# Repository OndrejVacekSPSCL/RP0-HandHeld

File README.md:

# RP0-HandHeld
>*This project was made for HackClub Highway*

Raspberry Pi Zero 2 gaming handheld, that runs Retro Pie...

I always wanted gaming console that has retro games in it so I made this!

## Repository Layout

The repo is structured as follows:
- PCB-related KiCad files in the `PCB/`
- KiCAD case design in `CAD/`
- Software related stuff is located in `Software/`
- For a rough BOM, see `BOM.csv`
- For my development log, see `JOURNAL.md`
- HackClub Readme is located in `README-original.md`
  
> [!CAUTION]
> The physical version of the console is not finished yet! The tutorial will be made after the completation.

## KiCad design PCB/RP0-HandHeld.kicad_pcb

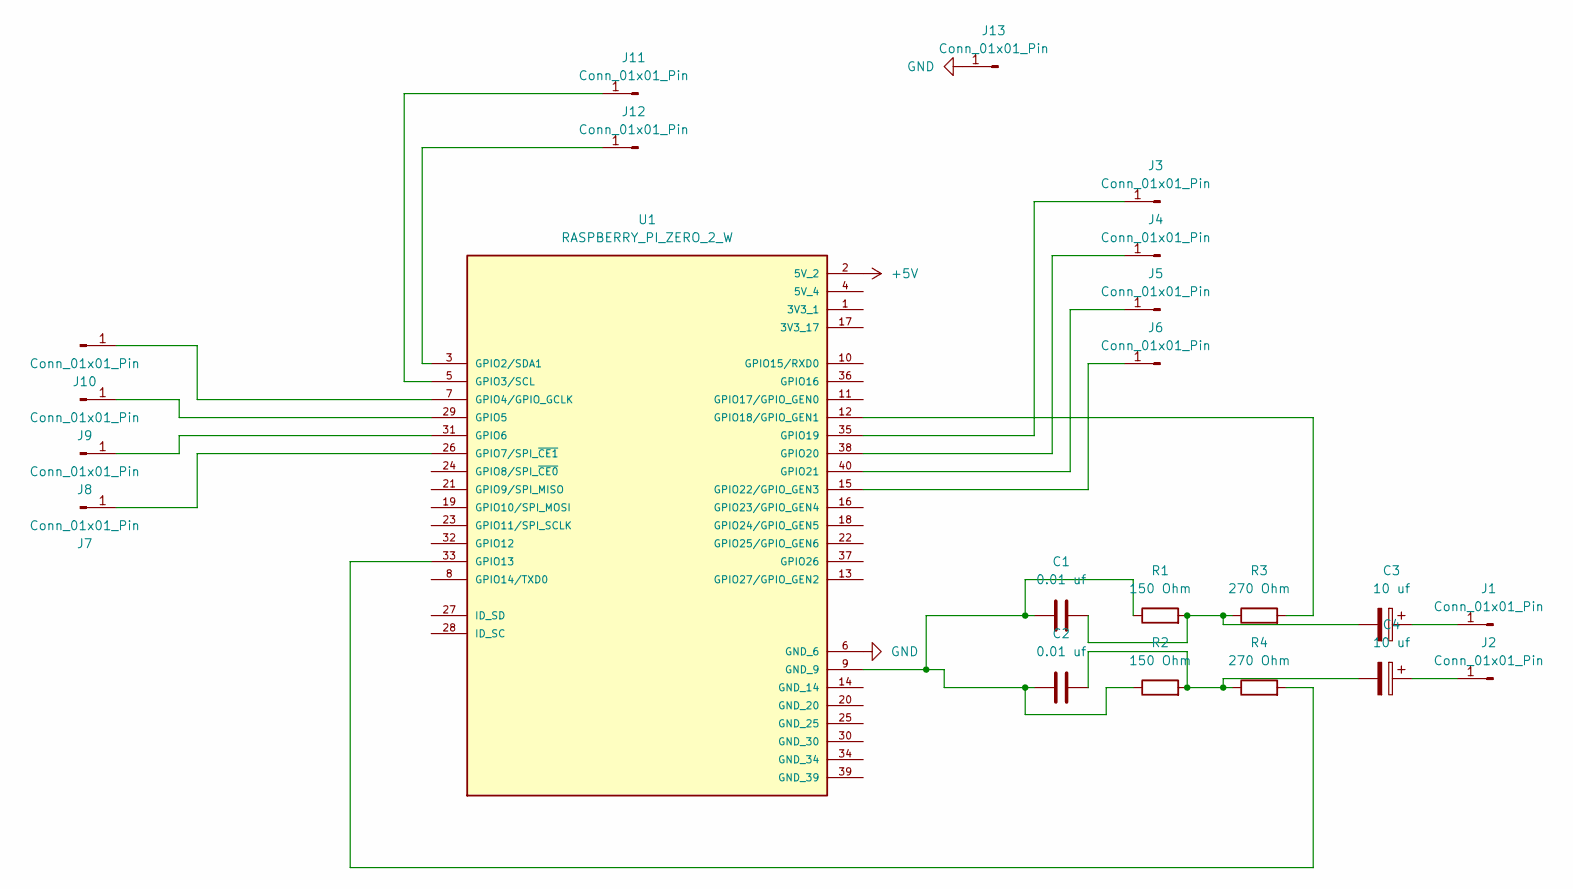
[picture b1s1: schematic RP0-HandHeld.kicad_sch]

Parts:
C1, C2: 0.01 uf; C_Disc_D5.0mm_W2.5mm_P5.00mm
C3, C4: 10 uf; CP_Radial_D4.0mm_P2.00mm
J1, J2, J3, J4, J5, J6, J7, J8, J9, J10, J11, J12, J13: Conn_01x01_Pin; SolderWire-0.5sqmm_1x01_D0.9mm_OD2.3mm
R1, R2: 150 Ohm; R_Axial_DIN0414_L11.9mm_D4.5mm_P15.24mm_Horizontal
R3, R4: 270 Ohm; R_Axial_DIN0414_L11.9mm_D4.5mm_P15.24mm_Horizontal
U1: RASPBERRY_PI_ZERO_2_W; MODULE_RASPBERRY_PI_ZERO_2_W; PARTREV April 2024

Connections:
+5V: U1.2 (5V_2)
GND: J13.1, U1.6 (GND_6)
unnamed: C1.2, C3.2, R1.2, R3.1
unnamed: C2.2, C4.2, R2.2, R4.1
unnamed: C3.1, J1.1
unnamed: C4.1, J2.1
unnamed: J3.1, U1.35 (GPIO19)
unnamed: J4.1, U1.38 (GPIO20)
unnamed: J5.1, U1.40 (GPIO21)
unnamed: J6.1, U1.15 (GPIO22/GPIO_GEN3)
unnamed: J7.1, U1.26 (GPIO7/SPI_~CE1)
unnamed: J8.1, U1.31 (GPIO6)
unnamed: J9.1, U1.29 (GPIO5)
unnamed: J10.1, U1.7 (GPIO4/GPIO_GCLK)
unnamed: J11.1, U1.5 (GPIO3/SCL)
unnamed: J12.1, U1.3 (GPIO2/SDA1)
unnamed: C1.1, C2.1, R1.1, R2.1, U1.9 (GND_9)
unnamed: R4.2, U1.33 (GPIO13)
unnamed: R3.2, U1.12 (GPIO18/GPIO_GEN1)

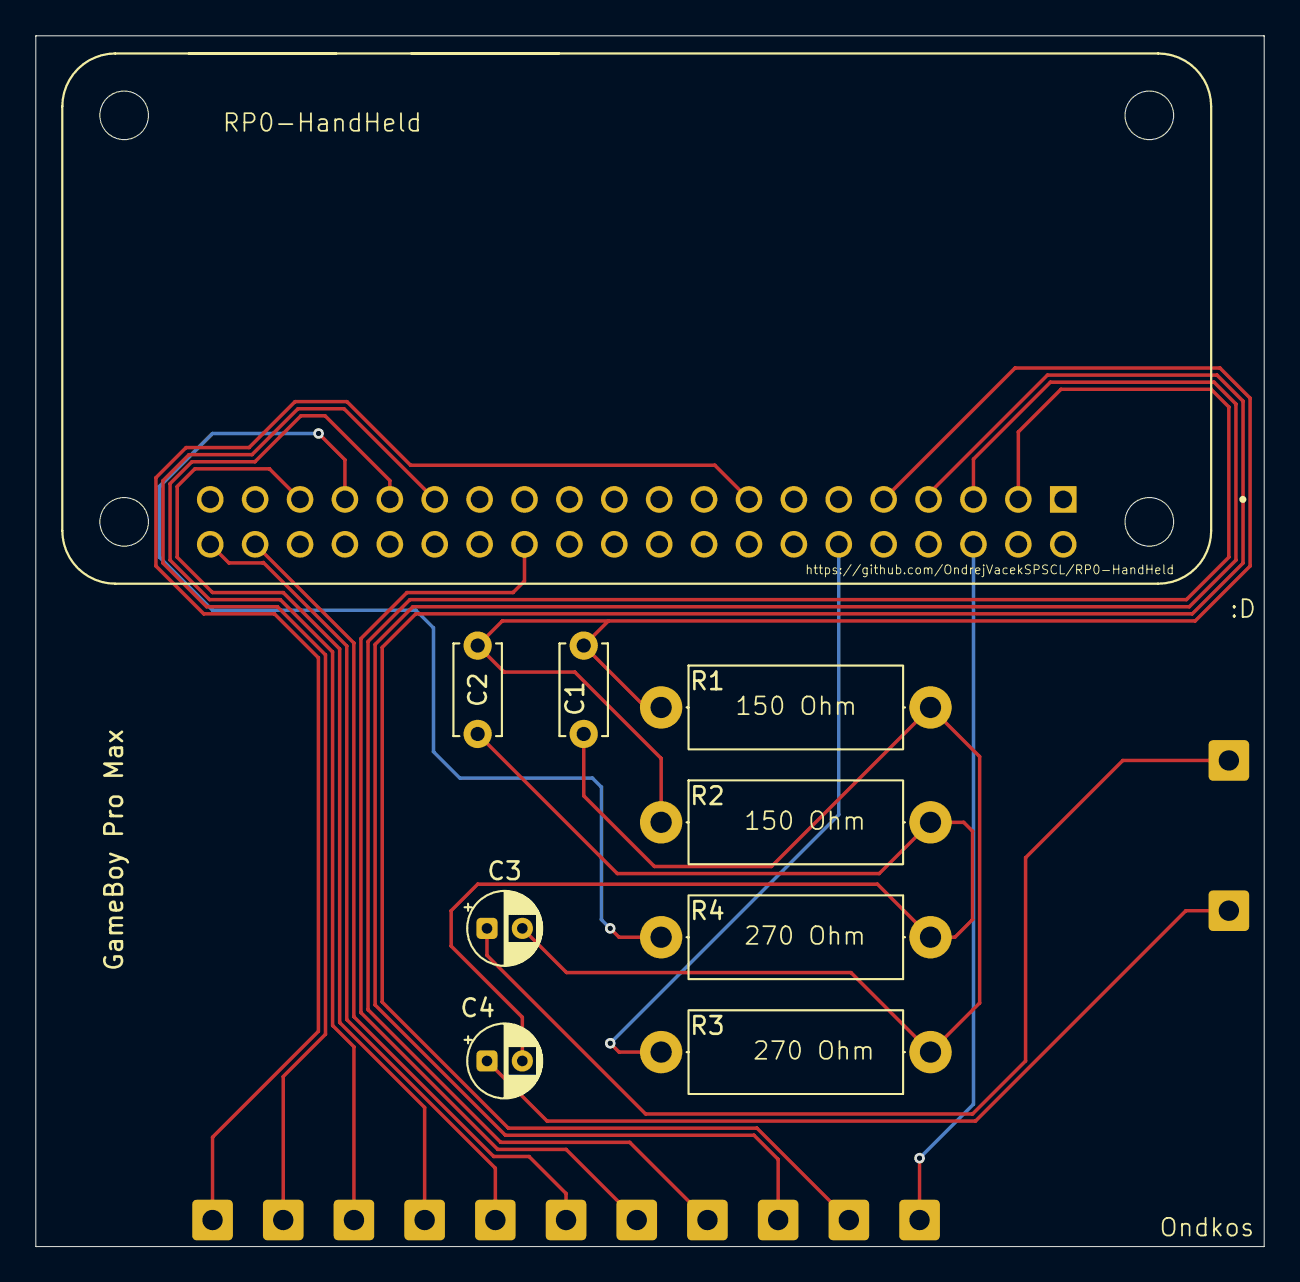
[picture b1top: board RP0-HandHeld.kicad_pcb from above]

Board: 2 copper layers, 69.5 x 68.5 mm, 22 parts (0 on the bottom side), 18 nets.

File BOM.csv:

Part,Quantity needed,Quantity in set,Price(USD),Shipping(USD),Note,Link
Raspberry Pi zero 2W,1,1,30.65,Free,,https://www.aliexpress.com/item/1005005876463565.html?spm=a2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
Touch screen,1,1,31.41,8.95,,https://www.aliexpress.com/item/1005007372530555.html?spm=a2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
270 Ohm resistors,2,20,0.87,1.20,,https://www.aliexpress.com/item/1005006546596146.html?spm=a2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
150 Ohm resistors,2,20,0.87,1.20,,http://aliexpress.com/item/1005006546596146.html?spm=a2g0o.p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
10 uf electrolitic Capacitors,2,20,1.23,Free,,https://www.aliexpress.com/item/32895970824.html?spm=a2g0o.p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
0.01 uf Polyester-Film Capacitors(103J),2,30,2.50,Free,,https://www.aliexpress.com/item/1005007139328345.html?spm=a2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
Speaker,1,2,3.95,Free,,https://www.aliexpress.com/item/1005007111833167.html?spm=a2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,scm-url:1007.40196.439370.0,pvid:4dfe8dde-b445-4008-ba0b-1159de657025,tpp_buckets:668%232846%238115%232000&pdp_ext_f=%7B%22order%22%3A%22289%22%2C%22eval%22%3A%221%22%2C%22sceneId%22%3A%2230050%22%7D&utparam-url=scene%3ApcDetailTopMoreOtherSeller%7Cquery_from%3A
PCB,1,1,NaN,NaN,,
Switches,10,10,1.03,1.08,,https://www.aliexpress.com/item/32866761020.html
Wires(28AWG),1,1,3.00,Free,,https://www.aliexpress.com/item/1005007009685328.html?spm=a2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
Battery,1,1,13.82,Free,,https://www.aliexpress.com/item/1005008087303778.html?spm=a2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
PWR Switch,1,5,1.63,Free,,https://www.aliexpress.com/item/32873386670.html?spm=a2g0o.p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
Voltage booster(5V),1,1,0.94,0.48,,https://www.aliexpress.com/item/1005006342017830.html?spm=a2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
USB-C inupt with cables,1,5,2.33,Free,,https://www.aliexpress.com/item/1005007469640237.html?spm=a2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
Battery charge indicator(1S),1,1,0.94,0.65,,https://www.aliexpress.com/item/1005006713968836.html?spm=a2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


Total,,,108,74,,Price with shipping,

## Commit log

2025-05-28 Created PCB folder
2025-05-28 Created PCB schematic
2025-05-28 Started working on the pcb
2025-05-28 Finished PCB
2025-05-28 Added gitignore for KiCad
2025-05-29 Redesigned the PCB
2025-05-29 Edited silkscreen PCB
2025-06-03 added software folder
2025-06-26 Render
2025-06-26 production files added
2025-09-05 Added assets folder
2025-09-05 temp
2025-09-08 New case
